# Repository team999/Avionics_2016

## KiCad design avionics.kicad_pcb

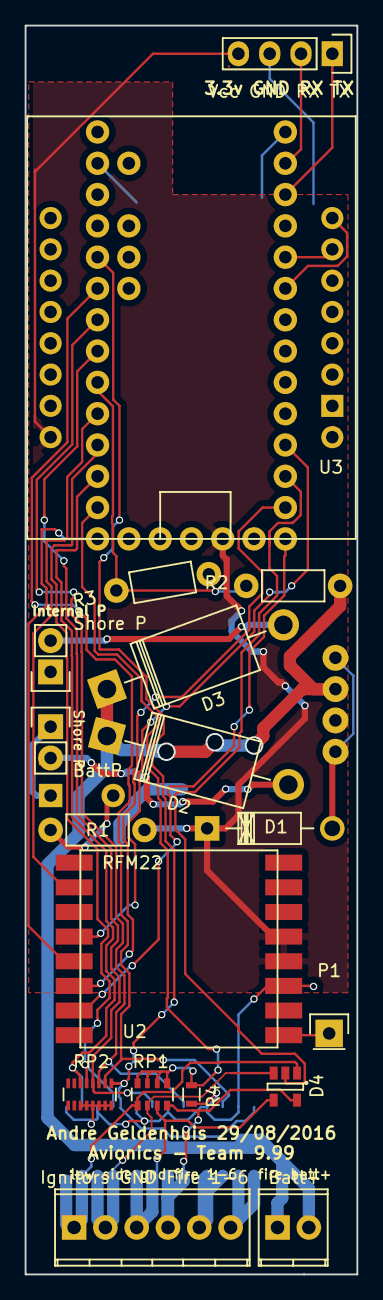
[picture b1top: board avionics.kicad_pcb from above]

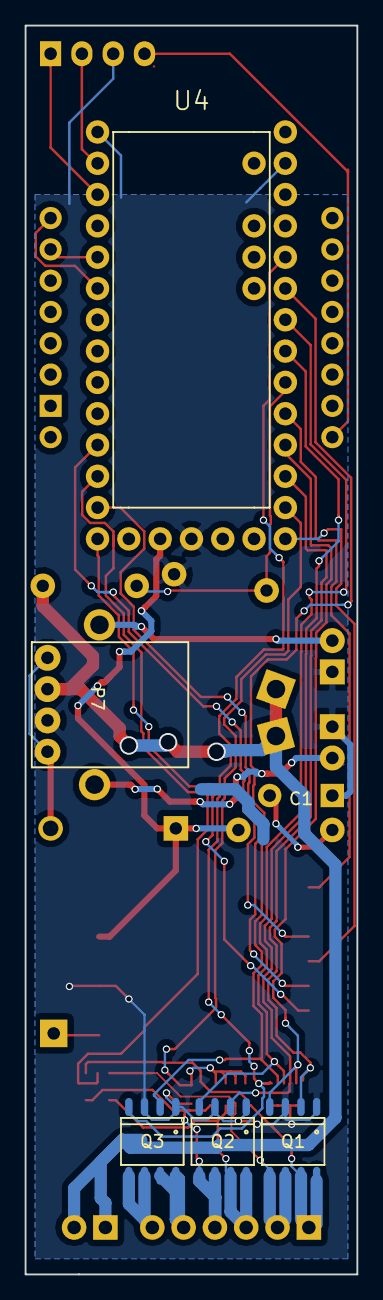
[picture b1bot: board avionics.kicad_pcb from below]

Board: 2 copper layers, 26.9 x 101.3 mm, 24 parts (6 on the bottom side), 32 nets.

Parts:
Batt+: Positive_fire_circuits; TerminalBlock_Pheonix_MPT-2.54mm_2pol
BattP: Internal_battery_power; Pin_Header_Straight_1x02
C1: CP; 4F_radial_supercap_mod
D1: D; Diode_DO-41_SOD81_Horizontal_RM10
D2, D3: D; Diode_DO-201AD_Horizontal_RM15
D4: Diode_pack_4; SOT-23-5
Ignitors GND Fire 1-6: FireCircuits; TerminalBlock_Pheonix_MPT-2.54mm_6pol
P1: Ant; Pin_Header_Straight_1x01
P7: D24V5F3; Polulu_D24V5F3
Q1, Q2, Q3: BUK9K45-100E; SO-8
R1, R2, R3: R; Resistor_Horizontal_RM7mm
R4: R; R_0603
RP1: R_PACK4; R_Array_Convex_4x0603
RP2: R_PACK8; R_Array_Convex_8x0602
Shore P: Shore_power; Pin_Header_Straight_1x02
U2: RFM22
U3: WeMos_mini; D1_mini_Pin_Header
U4: Teensy_3.1; Teensy-3.1
Vcc GND RX TX: GPS Connector; Pin_Header_Straight_1x04

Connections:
+3V3: D1.1, R1.2, U2.4, U2.5, U3.16, U4.31, Vcc GND RX TX.4
+BATT: Batt+.1, Batt+.2, D2.1, D3.1, P7.2, R2.1
/Aux1: Q3.2, RP2.2, U4.21
/Aux2: Q3.4, RP2.1, U4.22
/Fire1: Q1.2, RP2.6, U4.15
/Fire2: Q1.4, RP2.5, U4.16
/Fire3: Q2.2, RP2.4, U4.19
/Fire4: Q2.4, RP2.3, U4.20
/Firing_circuits/Cont1: D4.2, U4.10
/Sense: R4.2, RP1.1, RP1.2, RP1.3, RP1.4, U4.14
GND: BattP.1, C1.2, P7.3, Q1.1, Q1.3, Q2.1, Q2.3, Q3.1, Q3.3, R3.2, R4.1, RP2.11, RP2.12, RP2.13, RP2.14, RP2.15, RP2.16, Shore P.1, U2.3, U4.25, U4.27, U4.30, Vcc GND RX TX.3
unnamed: C1.1, R1.1
unnamed: D1.2, P7.1, P7.4
unnamed: D2.2, Shore P.2
unnamed: BattP.2, D3.2
unnamed: D4.1, Ignitors GND Fire 1-6.1, Q1.7, Q1.8, RP1.5
unnamed: D4.3, Ignitors GND Fire 1-6.2, Q1.5, Q1.6, RP1.6
unnamed: D4.4, Ignitors GND Fire 1-6.3, Q2.7, Q2.8, RP1.7
unnamed: D4.5, Ignitors GND Fire 1-6.4, Q2.5, Q2.6, RP1.8
unnamed: P1.1, U2.1
unnamed: U4.1, Vcc GND RX TX.1
unnamed: U4.0, Vcc GND RX TX.2
unnamed: Ignitors GND Fire 1-6.5, Q3.7, Q3.8
unnamed: Ignitors GND Fire 1-6.6, Q3.5, Q3.6
unnamed: R2.2, R3.1, U4.18
unnamed: U2.10, U4.12
unnamed: U2.11, U4.11
unnamed: U2.12, U4.13
unnamed: U2.13, U4.9
unnamed: U2.15, U4.17
unnamed: U3.7, U4.3
unnamed: U3.8, U4.4

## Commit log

2016-08-28 Ignore bakup files
2016-08-28 Initial schematic draught
2016-08-29 Increased gitigore coverage
2016-08-29 Initial design with traces - a little bit gross
